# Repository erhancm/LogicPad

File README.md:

<h1 align="center">LogicPad</h1>

<p align="center">
  <strong>A programmable USB macro pad — and a desktop app that makes it yours.</strong><br>
  Assign macros, build lighting profiles, auto-switch layouts per app, back up your setups, and update firmware — all over USB.
</p>

<p align="center">

</p>

<p align="center">
  <a href="#-logicpad-configurator">Configurator</a> ·
  <a href="#-features">Features</a> ·
  <a href="#-hardware">Hardware</a> ·
  <a href="#-quick-start">Quick start</a> ·
  <a href="https://git.erhancm.com/erhan/LogicPad/releases">Download app</a>
</p>

---

## 💻 LogicPad configurator

LogicPad shows up as a standard USB keyboard when you plug it in, so it works without any software. The **Windows, macOS, and Linux** configurator app (built with Tauri 2) gives you a full-screen key editor, YAML profile packs, automatic profile switching based on which app you're using, and **firmware updates over USB**.

<table>
  <tr>
    <td colspan="2" align="center">
      
      <br><sub><b>Keys</b> — macros, chords, typed text, and drag-and-drop PC program launch</sub>
    </td>
  </tr>
  <tr>
    <td width="50%" align="center">
      
      <br><sub><b>Profiles</b> — wave, ripple, breathe &amp; rain lighting · per-key colours · OLED settings</sub>
    </td>
    <td width="50%" align="center">
      
      <br><sub><b>Auto-switch</b> — switch profiles when you focus or run specific apps</sub>
    </td>
  </tr>
</table>

### Try it without hardware

The app has a built-in simulated LogicPad so you can try everything without owning the physical board. Note that the software is still a work in progress — some features aren't implemented yet.

### Install the app

Download from **[Releases](https://git.erhancm.com/erhan/LogicPad/releases)**:

| Platform | Download | Install |
|----------|----------|---------|
| **Windows** | `LogicPad_*_x64-setup.exe` | Run the installer |
| **macOS** | `LogicPad_*_x64.dmg` | Open the DMG, drag LogicPad to Applications |
| **Linux** | `LogicPad_*_amd64.AppImage` | `chmod +x LogicPad_*.AppImage && ./LogicPad_*.AppImage` |
| **Linux** | `logicpad-app_*_amd64.deb` | `sudo apt install ./logicpad-app_*_amd64.deb` |
| **All** | `LogicPad-Productivity.yaml` | Import in the app (**Import…**) Example configuration |

**Linux note:** You'll need to install a [udev rule](04%20Software/logicpad-app/README.md#linux-udev) so the app has permission to communicate with the pad over USB. Without it, the app can't detect the device.

**Build from source:** `cd "04 Software/logicpad-app" && npm install && npm run build:app`

**Showcase demo:** [`04 Software/logicpad-app/showcase/`](04%20Software/logicpad-app/showcase/) comes with five pre-built profiles.

**Full app docs:** [`04 Software/logicpad-app/README.md`](04%20Software/logicpad-app/README.md)

---

## 🎯 Features

| | |
|---|---|
| **Keys** | A 3×3 grid of macro keys. Each key can trigger a keyboard shortcut, mouse click, media control or typed string (up to 240 bytes per key). You can also launch a PC program directly from a key. |
| **Profiles** | Create as many profiles as the internal flash allows. Each profile has its own lighting mode (wave, ripple, breathe, rain) or per-key RGB colours. |
| **Auto-switch** | A visual node graph lets you define rules like "when Spotify is focused, switch to the Media profile." Supports foreground-app and running-app checks, AND/OR logic gates.
| **YAML packs** | Export your entire setup — profiles, key mappings, and auto-switch rules — to a single YAML file. Import it later or share it with others. Use **Save as…** / **Import…** in the app. |
| **On-board bootloader** | Every board has a 4 KB USB HID bootloader. After the first flash, you can update firmware straight from the app — no ST-Link or disassembly needed. If something goes wrong, hold **SEL** while plugging in to enter recovery mode. |
| **On-device OLED editor** | Don't have the app? You can configure keys, profiles, and settings entirely from the pad's OLED screen using the selector and the nine keys as a d-pad. |
| **Plug-and-play HID** | LogicPad appears as a standard USB keyboard, mouse, and media device. No custom drivers needed on Windows, macOS, or Linux. |
| **Open hardware** | Full KiCad schematic and PCB layout. |

---

## 🔩 Hardware

<p align="center">
  <em>9 macro keys + selector · 0.96″ OLED · per-key RGB · STM32F103 · 3D-printable enclosure</em>
</p>

| Spec | Detail |
|------|--------|
| MCU | STM32F103C8 (ARM Cortex-M3) — 64 KB flash, 20 KB RAM |
| Keys | 9 macro keys + 1 selector button |
| Display | 0.96″ SSD1306 OLED, 128×64 pixels, connected over I²C |
| Lighting | Per-key RGB using 2020-size LEDs |
| USB | Composite HID device — keyboard + mouse + media controls + vendor-specific reports for app communication |
| Flash map | **4 KB** bootloader · **52 KB** application · **8 KB** persistent config store |

Current hardware revision: **V0.2** in [`02 Electronics/V0.2/`](02%20Electronics/V0.2/).

### Firmware updates

Every LogicPad board has a **4 KB USB HID bootloader** baked into flash. Once the board has been programmed for the first time, all future firmware updates happen over a regular USB cable — no ST-Link, no SWD debugger, and no need to open the enclosure.

**Updating firmware:**

1. Build the application firmware with the `Release` CMake preset in [`03 Firmware/Firmware/`](03%20Firmware/Firmware/).
2. Open the configurator app, click **Update firmware**, and select your `LogicPad.bin` file. The app communicates with the bootloader over USB HID and flashes the new image.

**Recovery:** If a firmware update fails or the app won't boot, hold the **SEL** button while plugging in the USB cable. This forces the board into bootloader mode so you can re-flash.

**First-time programming** still requires an ST-Link programmer (one-time only). The factory image `LogicPad_factory.hex` bundles both the bootloader and the application. See [`03 Firmware/bootloader/README.md`](03%20Firmware/bootloader/README.md) for details.

---

## 🚀 Quick start

### Daily use (no app needed)

1. **Plug in USB.** The host OS recognises LogicPad as a standard HID keyboard (plus mouse and media controls if you've configured them). No drivers, no pairing — it just works.

2. **Navigate the OLED menus.** A short press on the **selector** (SEL) button opens the on-device menu. Inside menus, the nine keys double as a d-pad for navigation:

   <table>
     <tr>
       <td width="55%">
         <table>
           <tr><th>Key</th><th>Action</th></tr>
           <tr><td>2</td><td>Up</td></tr>
           <tr><td>8</td><td>Down</td></tr>
           <tr><td>4</td><td>Left</td></tr>
           <tr><td>6</td><td>Right</td></tr>
           <tr><td>5</td><td>OK (select)</td></tr>
         </table>
         <p><strong>Short press SEL</strong> = go back one level. 
       </td>
       <td width="45%" align="center">
         
       </td>
     </tr>
   </table>

3. **Assign your macros.** Factory boards ship with empty key slots. You can assign macros either from the OLED menu (no PC required) or from the app. The app has more options.

### Build firmware from source

You'll need an ARM GCC toolchain and CMake. Both the bootloader and application firmware use CMake presets.

1. **Build the bootloader** — open [`03 Firmware/bootloader/`](03%20Firmware/bootloader/) and build with the `Release` CMake preset.
2. **Build the application** — open [`03 Firmware/Firmware/`](03%20Firmware/Firmware/) and build with the `Release` CMake preset.
3. **First-time flash** — combine bootloader + app into `LogicPad_factory.hex` and flash it via ST-Link (this is the only time you need ST-Link).
4. **All later updates** — just click **Update firmware** in the configurator app and point it at your new `LogicPad.bin`. The on-board bootloader handles the rest over USB.

---

## 📁 Repository layout

The repo is organised by discipline, numbered so it sorts in a logical order:

| Path | Contents |
|------|----------|
| [`01 Documentation/`](01%20Documentation/) | Hardware and protocol docs — MCU pinout, HID report format, OLED menu structure, and C4 architecture diagrams. |
| [`02 Electronics/V0.2/`](02%20Electronics/V0.2/) | KiCad schematic and PCB layout for the current board revision, plus BOM and Gerber files for manufacturing. |
| [`03 Firmware/Firmware/`](03%20Firmware/Firmware/) | Production firmware for the STM32F103. CMake-based build with ARM GCC. Handles USB HID, key scanning, OLED display, RGB lighting, and config storage. |
| [`03 Firmware/bootloader/`](03%20Firmware/bootloader/) | On-board USB HID bootloader. Occupies the first 4 KB of flash and allows firmware updates over USB without a debugger. |
| [`04 Software/logicpad-app/`](04%20Software/logicpad-app/) | Desktop configurator app — Tauri 2 (Rust + web frontend). Handles key editing, profile management, auto-switch rules, YAML import/export, and firmware updates. |
| [`05 Hardware/`](05%20Hardware/) | 3D-printable enclosure — STEP files for the case and button caps. |
| [`.github/assets/`](.github/assets/) | Images used in this README. |

---

## 📖 Documentation

- [Pinout](01%20Documentation/Pinout.md) — MCU pin assignments, key matrix wiring, OLED connections, and RGB data lines
- [HID protocol](01%20Documentation/HID_PROTOCOL.md) — USB HID report format and vendor-specific commands used by the configurator app
- [OLED UI](01%20Documentation/OLED_UI.md) — on-device menu structure and navigation flow
- [C4 architecture](01%20Documentation/C4_MODEL.md) — high-level system overview in C4 model notation

---

## 🤝 Contributing

Contributions are welcome — whether it's a bug report, a feature request, or a pull request. If you're planning a larger change, it's worth opening an issue first to discuss the approach. By contributing, you agree that your contributions will be licensed under [Apache 2.0](LICENSE).

---

## 🐛 Known issues

| Issue | Type | Status | Notes |
|-------|------|--------|-------|
| Sometimes you can't pan across the node editor when clicking on an empty area and dragging the mouse | Software | Open | Needs more investigation |
| OLED flicker or banding when taking pictures with camera| Software | Open | To do with refresh rate |
| Standby Clock setting is not persistant | Firmware | Open | When powering the unit off and on, the standby clock is reset to the default setting |
| Not all standby clock styles work | Software + Firmware | Open | Needs more investigation |
| LEDs can't reach full brightness in custom lighting modes | Hardware | Open | The LEDs are scanned one key at a time (1/9 duty cycle), so each LED is only actually on for a fraction of the time — the rest just looks lit because of persistence of vision. The STM32F103's GPIO pins can't source enough current to drive all 27 LEDs (9 keys × 3 colours) at once, so the per-LED brightness is capped by the scan rate. |

---

## 📝 To-do

| Feature | Type | Status | Notes |
|---------|------|--------|-------|
| Custom scripting assignable to each button | Software | Planned | Python/Lua scripts — TBD |
| Mouse and keyboard recording | Software | Planned | Record input sequences and replay them from a key |
| OCR-based automation | Software | Planned | Use image recognition to perform actions based on what's on screen |
| Long press functions | Software + Firmware | Planned | Different actions for short vs. long key presses |
| Profile hotkeys | Firmware | Planned | Assign a key to cycle through or jump to specific profiles instead of going through the on-board menu (temporarily override auto-switch condition) |

### Hardware V0.3

| Feature | Status | Notes |
|---------|--------|-------|
| Upgrade MCU to STM32F4 or RP2040 | Planned | More flash and RAM for larger configs, scripting support, and faster USB |
| USB-C connector | Planned | Replace the current Micro-USB with USB-C for better durability and reversibility |
| Hot-swap key sockets | Planned | Swap switches without soldering |
| Per-key addressable LEDs (WS2812B) | Planned | Remove the 1/9 scanning limitation and allow full brightness on all keys simultaneously |
| Larger OLED display | Planned | Upgrade from 0.96″ to 1.3″ for more readable menus and more info on screen |
| Rotary encoder | Planned | Add a clickable rotary encoder for volume control, scrolling, or menu navigation |
| Slider potentiometer | Planned | Linear slider for volume, brightness, or other continuous control |
| External flash storage | Planned | Dedicated flash chip or SD card slot — TBD. Would allow storing more profiles, macros, and recorded scripts on-device |
| Temperature and humidity sensor | Planned | Environmental sensor for ambient readings displayed on the OLED or used in automation rules. Including support for logging |

---

## 📄 License

This project is licensed under the [Apache License 2.0](LICENSE).

The third-party libraries bundled in `03 Firmware/Firmware/Drivers/` — namely the STM32 HAL, CMSIS, and ST's USB device library — are not covered by this license. They remain under their respective upstream licenses from STMicroelectronics and ARM.

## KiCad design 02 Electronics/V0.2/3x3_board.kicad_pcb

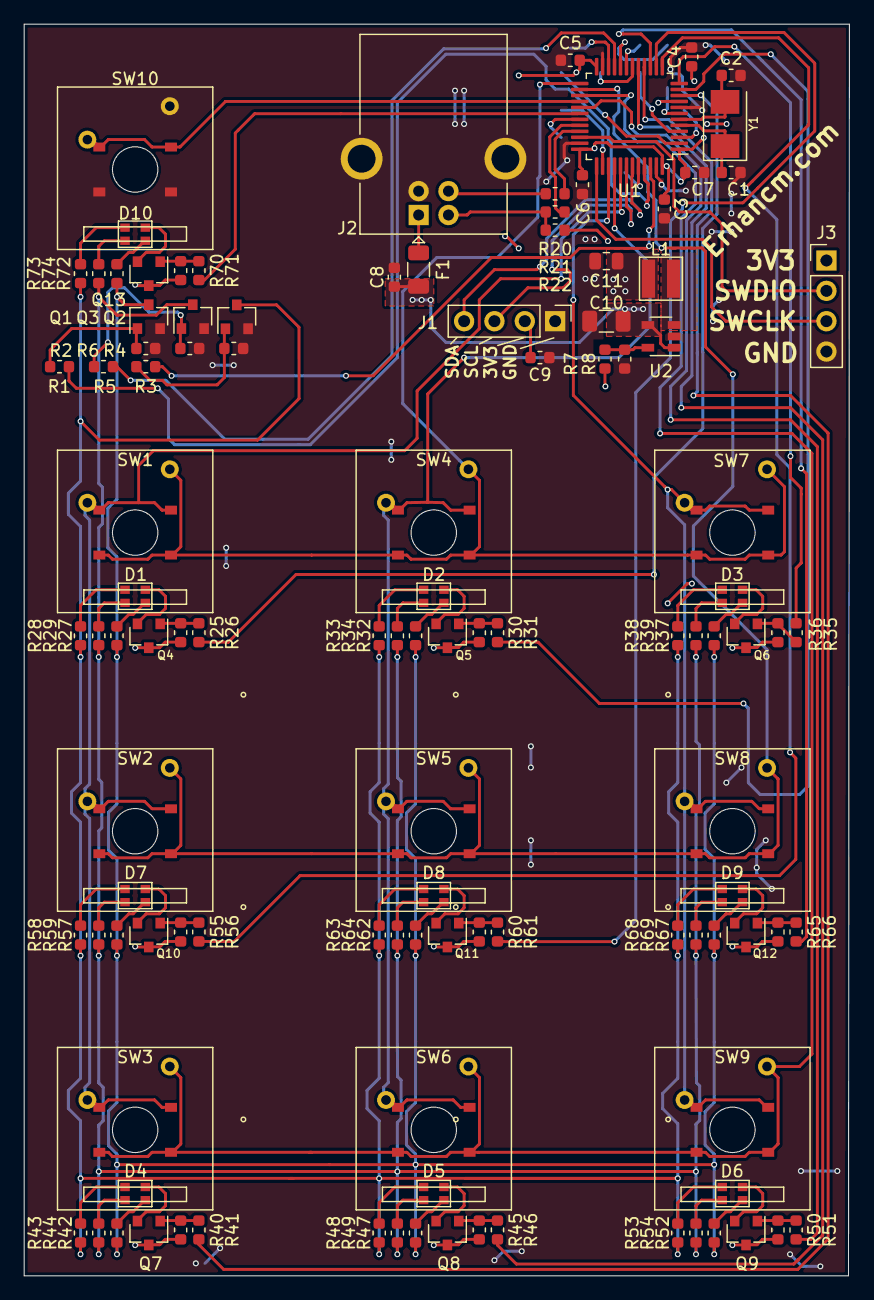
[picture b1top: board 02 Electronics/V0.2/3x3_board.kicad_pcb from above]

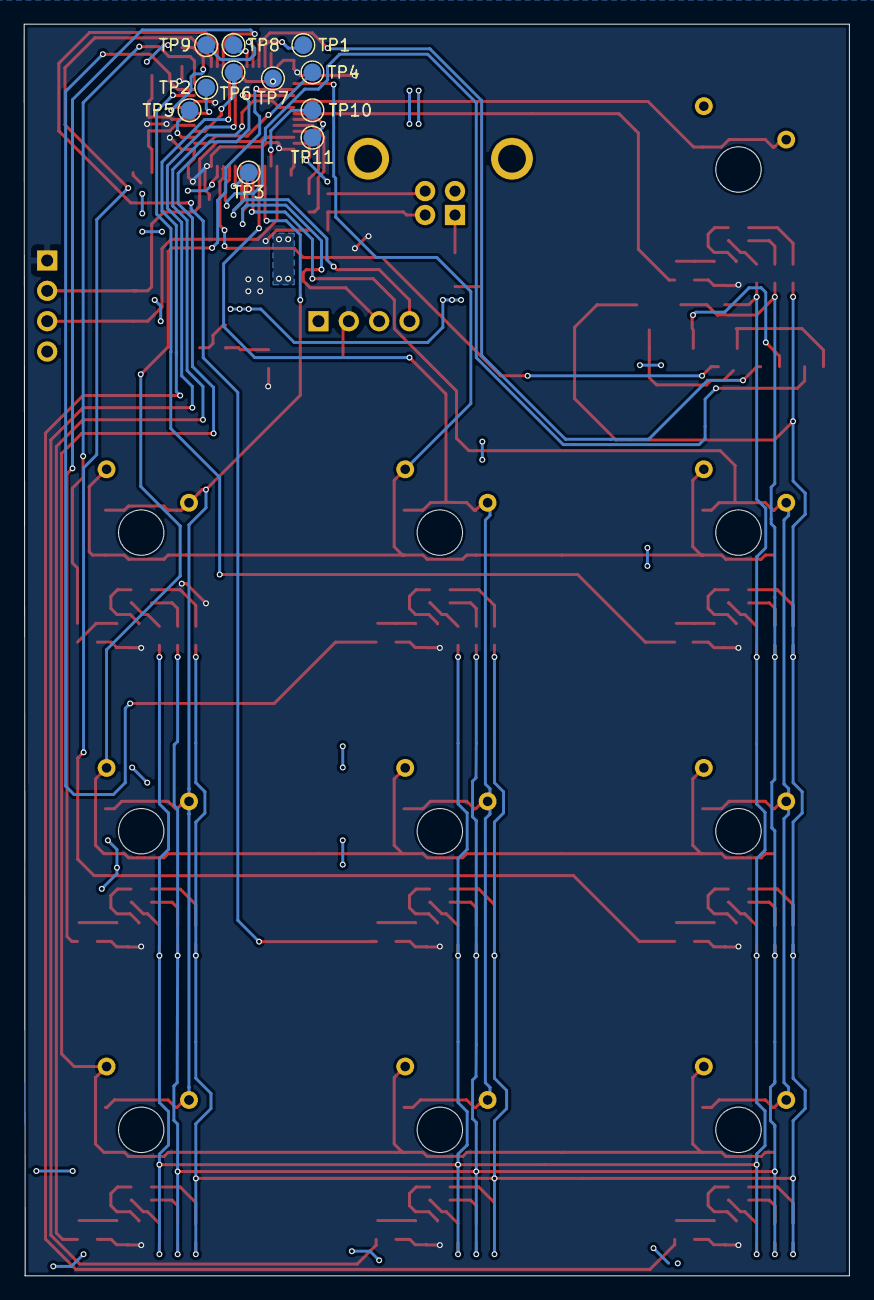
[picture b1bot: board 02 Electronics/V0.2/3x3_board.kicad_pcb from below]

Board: 2 copper layers, 69.1 x 104.8 mm, 124 parts (11 on the bottom side), 103 nets.

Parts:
C1, C2: 12pF; C_0603_1608Metric
C3, C4, C5, C6, C7, C8, C9: 100n; C_0603_1608Metric
C10: 4.7uF; C_1206_3216Metric
C11: 22uF; C_0805_2012Metric
D1, D2, D3, D4, D5, D6, D7, D8, D9, D10: RGB_LED; 2020_RGB
F1: Fuse; Fuse_1206_3216Metric
J1, J3: Conn_01x04; PinHeader_1x04_P2.54mm_Vertical
J2: USB_B; USB_B_OST_USB-B1HSxx_Horizontal
L1: 1uH; SRN3012TA-1R0Y
Q1, Q2, Q3: 2N7002; SOT-23
Q4, Q5, Q6, Q7, Q8, Q9, Q10, Q11, Q12, Q13: BSS84; SOT-23
R1, R3, R5, R26, R31, R36, R41, R46, R51, R56, R61, R66, R71: 100; R_0603_1608Metric
R2, R4, R6, R25, R30, R35, R40, R45, R50, R55, R60, R65, R70: 47k; R_0603_1608Metric
R7: 453K; R_0603_1608Metric
R8: 100K; R_0603_1608Metric
R20, R21: 22; R_0603_1608Metric
R22: 10K; R_0603_1608Metric
R27, R28, R29, R32, R33, R34, R37, R38, R39, R42, R43, R44, R47, R48, R49, R52, R53, R54, R57, R58, R59, R62, R63, R64, R67, R68, R69, R72, R73, R74: 165; R_0603_1608Metric
SW1, SW2, SW3, SW4, SW5, SW6, SW7, SW8, SW9, SW10: SW_Push; gateronSwitch
TP1, TP2, TP3, TP4, TP5, TP6, TP7, TP8, TP9, TP10, TP11: TestPoint_Probe; TestPoint_Pad_D1.5mm
U1: STM32F103C8Tx; LQFP-48_7x7mm_P0.5mm
U2: TLV62568DBV; SOT-23-5
Y1: 8Mhz; Crystal_SMD_5032-2Pin_5.0x3.2mm

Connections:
+3V3: C3.1, C4.1, C5.1, C6.1, C7.1, C9.2, C11.1, J1.2, J3.1, L1.2, Q4.3, Q5.3, Q6.3, Q7.3, Q8.3, Q9.3, Q10.3, Q11.3, Q12.3, Q13.3, R7.1, R22.1, R25.2, R30.2, R35.2, R40.2, R45.2, R50.2, R55.2, R60.2, R65.2, R70.2, U1.1, U1.9, U1.24, U1.36, U1.48
+5V: C8.1, C10.1, F1.1, U2.1, U2.4
/B_Ctrl: R5.1, U1.21
/BlueChannel: Q3.3, R29.2, R34.2, R39.2, R44.2, R49.2, R54.2, R59.2, R64.2, R69.2, R74.2
/C0R0: R26.1, U1.10
/C0R1: R31.1, U1.11
/C0R2: R36.1, U1.12
/C1R0: R56.1, U1.13
/C1R1: R61.1, U1.14
/C1R2: R66.1, U1.15
/C2R0: R41.1, U1.16
/C2R1: R46.1, U1.17
/C2R2: R51.1, U1.29
/Column_0: SW1.2, SW2.2, SW3.2, U1.41
/Column_1: SW4.2, SW5.2, SW6.2, U1.40
/Column_2: SW7.2, SW8.2, SW9.2, U1.39
/CtrlLed: R71.1, U1.30
/D+: R20.2, U1.33
/D-: R21.2, U1.32
/G_Ctrl: R3.1, U1.46
/GreenChannel: Q2.3, R28.2, R33.2, R38.2, R43.2, R48.2, R53.2, R58.2, R63.2, R68.2, R73.2
/I2C1_SCL: J1.3, U1.42
/I2C1_SDA: J1.4, U1.43
/R_Ctrl: R1.1, U1.45
/RedChannel: Q1.3, R27.2, R32.2, R37.2, R42.2, R47.2, R52.2, R57.2, R62.2, R67.2, R72.2
/Row_0: SW1.1, SW4.1, SW7.1, U1.25
/Row_1: SW2.1, SW5.1, SW8.1, U1.26
/Row_2: SW3.1, SW6.1, SW9.1, U1.27
/SWCLK: J3.3, U1.37
/SWDIO: J3.2, U1.34
/Selector: SW10.2, U1.28
/USB_D+: J2.3, R20.1
/USB_D-: J2.2, R21.1, R22.2
GND: C1.2, C2.2, C3.2, C4.2, C5.2, C6.2, C7.2, C8.2, C9.1, C10.2, C11.2, J1.1, J2.4, J2.5, J3.4, Q1.2, Q2.2, Q3.2, R2.2, R4.2, R6.2, R8.2, SW10.1, U1.8, U1.23, U1.35, U1.47, U2.2
unnamed: C1.1, U1.5, Y1.1
unnamed: C2.1, U1.6, Y1.2
unnamed: D1.1, R27.1
unnamed: D1.2, R29.1
unnamed: D1.3, Q4.2
unnamed: D1.4, R28.1
unnamed: D2.1, R32.1
unnamed: D2.2, R34.1
unnamed: D2.3, Q5.2
unnamed: D2.4, R33.1
unnamed: D3.1, R37.1
unnamed: D3.2, R39.1
unnamed: D3.3, Q6.2
unnamed: D3.4, R38.1
unnamed: D4.1, R42.1
unnamed: D4.2, R44.1
unnamed: D4.3, Q7.2
unnamed: D4.4, R43.1
unnamed: D5.1, R47.1
unnamed: D5.2, R49.1
unnamed: D5.3, Q8.2
unnamed: D5.4, R48.1
unnamed: D6.1, R52.1
unnamed: D6.2, R54.1
unnamed: D6.3, Q9.2
unnamed: D6.4, R53.1
unnamed: D7.1, R57.1
unnamed: D7.2, R59.1
unnamed: D7.3, Q10.2
unnamed: D7.4, R58.1
unnamed: D8.1, R62.1
unnamed: D8.2, R64.1
unnamed: D8.3, Q11.2
unnamed: D8.4, R63.1
unnamed: D9.1, R67.1
unnamed: D9.2, R69.1
unnamed: D9.3, Q12.2
unnamed: D9.4, R68.1
unnamed: D10.1, R72.1
unnamed: D10.2, R74.1
unnamed: D10.3, Q13.2
unnamed: D10.4, R73.1
unnamed: F1.2, J2.1
unnamed: L1.1, U2.3
unnamed: Q1.1, R1.2, R2.1
unnamed: Q2.1, R3.2, R4.1
unnamed: Q3.1, R5.2, R6.1
unnamed: Q4.1, R25.1, R26.2
unnamed: Q5.1, R30.1, R31.2
unnamed: Q6.1, R35.1, R36.2
unnamed: Q7.1, R40.1, R41.2
unnamed: Q8.1, R45.1, R46.2
unnamed: Q9.1, R50.1, R51.2
unnamed: Q10.1, R55.1, R56.2
unnamed: Q11.1, R60.1, R61.2
unnamed: Q12.1, R65.1, R66.2
unnamed: Q13.1, R70.1, R71.2
unnamed: R7.2, R8.1, U2.5
unnamed: TP1.1, U1.22
unnamed: TP2.1, U1.7
unnamed: TP3.1, U1.44
unnamed: TP4.1, U1.2
unnamed: TP5.1, U1.3
unnamed: TP6.1, U1.4
unnamed: TP7.1, U1.18
unnamed: TP8.1, U1.19
unnamed: TP9.1, U1.20
unnamed: TP10.1, U1.38
unnamed: TP11.1, U1.31

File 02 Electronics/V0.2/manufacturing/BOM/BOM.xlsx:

Comment | Designator | Footprint
SW_Push | SW1,SW7,SW8,SW10,SW9,SW6,SW5,SW4,SW3,SW2 | SMD
100K | R8 | R_0603_1608Metric
453K | R7 | R_0603_1608Metric
2N7002 | Q2,Q3,Q1 | SOT-23
100n | C9,C8,C7,C6,C5,C4,C3 | C_0603_1608Metric
TestPoint_Probe | TP11,TP10,TP9,TP8,TP7,TP6,TP5,TP4,TP3,TP2,TP1 | TestPoint_Pad_D1.5mm
8Mhz | Y1 | Crystal_SMD_5032-2Pin_5.0x3.2mm
165 | R74,R73,R72,R69,R68,R67,R64,R63,R62,R59,R58,R57,R54,R53,R52,R49,R48,R47,R44,R43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 | R_0603_1608Metric
100 | R71,R66,R61,R56,R51,R46,R41,R36,R31,R26,R5,R3,R1 | R_0603_1608Metric
47k | R70,R65,R60,R55,R50,R45,R40,R35,R30,R25,R6,R4,R2 | R_0603_1608Metric
BSS84 | Q13,Q12,Q11,Q10,Q9,Q8,Q7,Q6,Q5,Q4 | SOT-23
RGB_LED | D10,D9,D8,D7,D6,D5,D4,D3,D2,D1 | SMD
USB_B | J2 | USB_B_OST_USB-B1HSxx_Horizontal
TLV62568DBV | U2 | SOT-23-5
STM32F103C8Tx | U1 | LQFP-48_7x7mm_P0.5mm
10K | R22 | R_0603_1608Metric
22 | R21,R20 | R_0603_1608Metric
1uH | L1 | SRN3012TA-1R0Y
Conn_01x04 | J3,J1 | PinHeader_1x04_P2.54mm_Vertical
Fuse | F1 | Fuse_1206_3216Metric
22uF | C11 | C_0805_2012Metric
4.7uF | C10 | C_1206_3216Metric
12pF | C2,C1 | C_0603_1608Metric

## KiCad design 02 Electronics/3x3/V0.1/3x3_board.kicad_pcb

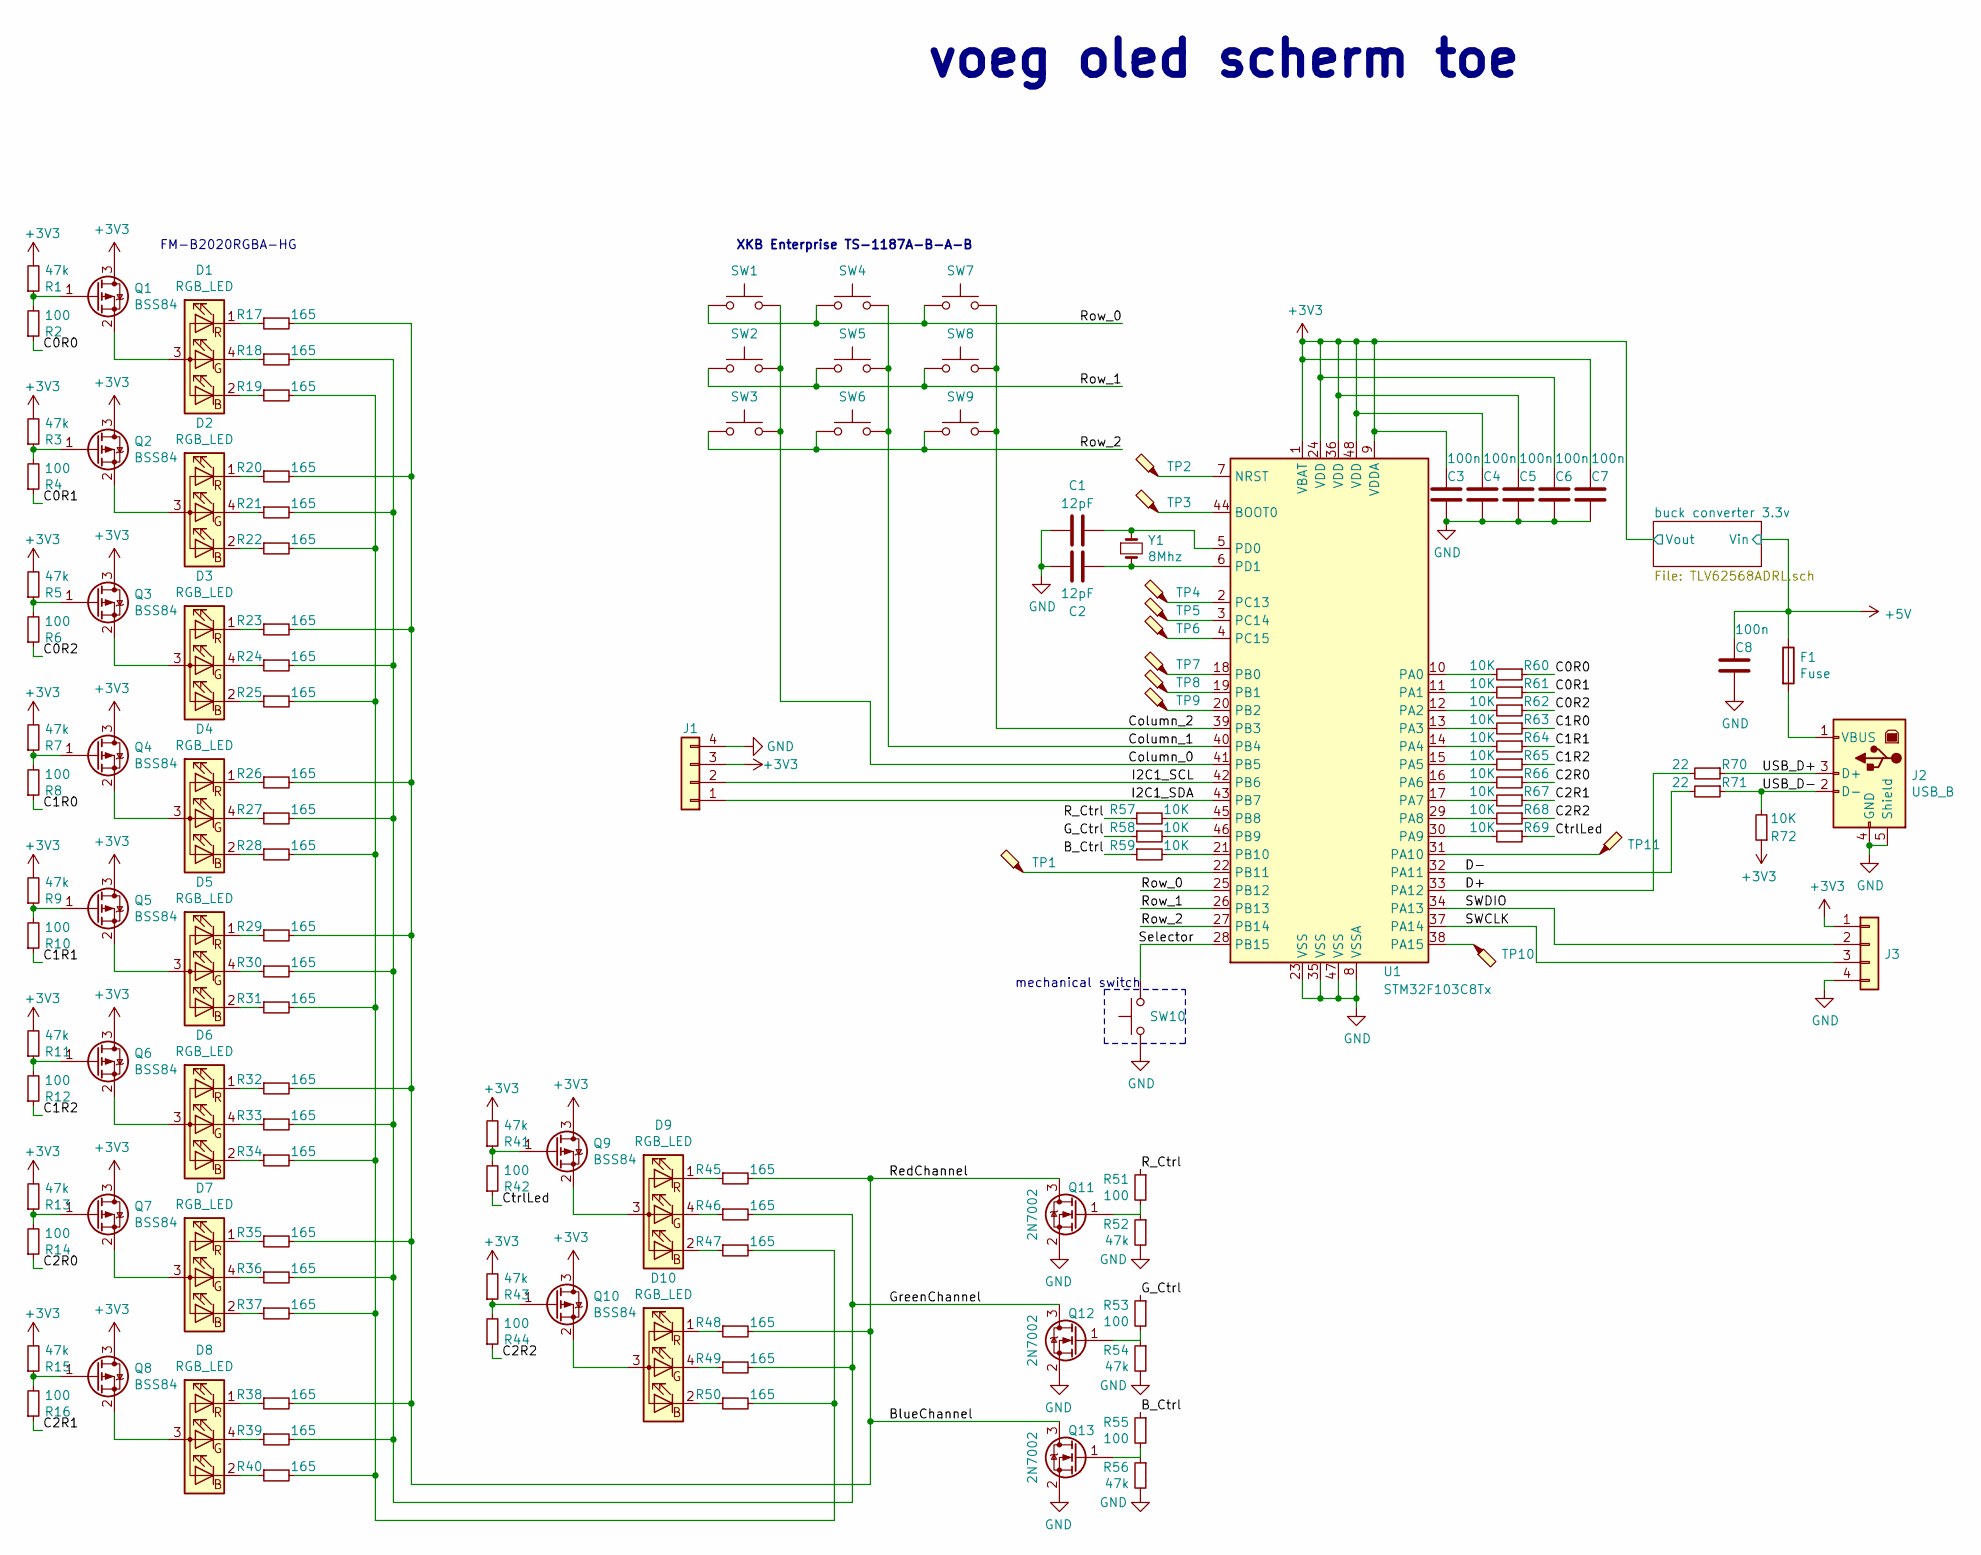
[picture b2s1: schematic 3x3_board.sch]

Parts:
C1, C2: 12pF; C_0603_1608Metric
C3, C4, C5, C6, C7, C8: 100n; C_0603_1608Metric
D1, D2, D3, D4, D5, D6, D7, D8, D9, D10: RGB_LED; 2020_RGB
F1: Fuse; Fuse_1206_3216Metric
J1, J3: Conn_01x04; PinHeader_1x04_P2.54mm_Vertical
J2: USB_B; USB_B_OST_USB-B1HSxx_Horizontal
Q1, Q2, Q3, Q4, Q5, Q6, Q7, Q8, Q9, Q10: BSS84; SOT-23
Q11, Q12, Q13: 2N7002; SOT-23
R1, R3, R5, R7, R9, R11, R13, R15, R41, R43, R52, R54, R56: 47k; R_0603_1608Metric
R2, R4, R6, R8, R10, R12, R14, R16, R42, R44, R51, R53, R55: 100; R_0603_1608Metric
R17, R18, R19, R20, R21, R22, R23, R24, R25, R26, R27, R28, R29, R30, R31, R32, R33, R34, R35, R36, R37, R38, R39, R40, R45, R46, R47, R48, R49, R50: 165; R_0603_1608Metric
R57, R58, R59, R60, R61, R62, R63, R64, R65, R66, R67, R68, R69, R72: 10K; R_0603_1608Metric
R70, R71: 22; R_0603_1608Metric
SW1, SW2, SW3, SW4, SW5, SW6, SW7, SW8, SW9, SW10: SW_Push; gateronSwitch
TP1, TP2, TP3, TP4, TP5, TP6, TP7, TP8, TP9, TP10, TP11: TestPoint_Probe; TestPoint_Loop_D1.80mm_Drill1.0mm_Beaded
U1: STM32F103C8Tx; LQFP-48_7x7mm_P0.5mm
Y1: 8Mhz; Crystal_SMD_5032-4Pin_5.0x3.2mm

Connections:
+3V3: C3.1, C4.1, C5.1, C6.1, C7.1, J1.3, J3.1, Q1.3 (D), Q2.3 (D), Q3.3 (D), Q4.3 (D), Q5.3 (D), Q6.3 (D), Q7.3 (D), Q8.3 (D), Q9.3 (D), Q10.3 (D), R1.2, R3.2, R5.2, R7.2, R9.2, R11.2, R13.2, R15.2, R41.2, R43.2, R72.1, U1.1 (VBAT), U1.9 (VDDA), U1.24 (VDD), U1.36 (VDD), U1.48 (VDD); also elsewhere on the board
+5V: C8.1, F1.1; also elsewhere on the board
/B_Ctrl: R55.1, R59.1
/BlueChannel: Q11.3 (D), Q13.3 (D), R17.2, R20.2, R23.2, R26.2, R29.2, R32.2, R35.2, R38.2, R45.2, R48.2
/C0R0: R2.1, R60.1
/C0R1: R4.1, R61.1
/C0R2: R6.1, R62.1
/C1R0: R8.1, R63.1
/C1R1: R10.1, R64.1
/C1R2: R12.1, R65.1
/C2R0: R14.1, R66.1
/C2R1: R16.1, R67.1
/C2R2: R44.1, R68.1
/Column_0: SW1.2, SW2.2, SW3.2, U1.41 (PB5)
/Column_1: SW4.2, SW5.2, SW6.2, U1.40 (PB4)
/Column_2: SW7.2, SW8.2, SW9.2, U1.39 (PB3)
/CtrlLed: R42.1, R69.1
/D+: R70.2, U1.33 (PA12)
/D-: R71.2, U1.32 (PA11)
/G_Ctrl: R53.1, R58.1
/GreenChannel: Q12.3 (D), R18.2, R21.2, R24.2, R27.2, R30.2, R33.2, R36.2, R39.2, R46.2, R49.2
/I2C1_SCL: J1.2, U1.42 (PB6)
/I2C1_SDA: J1.1, U1.43 (PB7)
/R_Ctrl: R51.1, R57.1
/Row_0: SW1.1, SW4.1, SW7.1, U1.25 (PB12)
/Row_1: SW2.1, SW5.1, SW8.1, U1.26 (PB13)
/Row_2: SW3.1, SW6.1, SW9.1, U1.27 (PB14)
/SWCLK: J3.3, U1.37 (PA14)
/SWDIO: J3.2, U1.34 (PA13)
/Selector: SW10.2, U1.28 (PB15)
/USB_D+: J2.3 (D+), R70.1
/USB_D-: J2.2 (D-), R71.1, R72.2
GND: C1.2, C2.2, C3.2, C4.2, C5.2, C6.2, C7.2, C8.2, J1.4, J2.4 (GND), J2.5 (Shield), J3.4, Q11.2 (S), Q12.2 (S), Q13.2 (S), R52.2, R54.2, R56.2, SW10.1, U1.8 (VSSA), U1.23 (VSS), U1.35 (VSS), U1.47 (VSS); also elsewhere on the board
unnamed: C1.1, U1.5 (PD0), Y1.1
unnamed: C2.1, U1.6 (PD1), Y1.2
unnamed: D1.1 (RK), R17.1
unnamed: D1.2 (BK), R19.1
unnamed: D1.3 (A), Q1.2 (S)
unnamed: D1.4 (GK), R18.1
unnamed: D2.1 (RK), R20.1
unnamed: D2.2 (BK), R22.1
unnamed: D2.3 (A), Q2.2 (S)
unnamed: D2.4 (GK), R21.1
unnamed: D3.1 (RK), R23.1
unnamed: D3.2 (BK), R25.1
unnamed: D3.3 (A), Q3.2 (S)
unnamed: D3.4 (GK), R24.1
unnamed: D4.1 (RK), R26.1
unnamed: D4.2 (BK), R28.1
unnamed: D4.3 (A), Q4.2 (S)
unnamed: D4.4 (GK), R27.1
unnamed: D5.1 (RK), R29.1
unnamed: D5.2 (BK), R31.1
unnamed: D5.3 (A), Q5.2 (S)
unnamed: D5.4 (GK), R30.1
unnamed: D6.1 (RK), R32.1
unnamed: D6.2 (BK), R34.1
unnamed: D6.3 (A), Q6.2 (S)
unnamed: D6.4 (GK), R33.1
unnamed: D7.1 (RK), R35.1
unnamed: D7.2 (BK), R37.1
unnamed: D7.3 (A), Q7.2 (S)
unnamed: D7.4 (GK), R36.1
unnamed: D8.1 (RK), R38.1
unnamed: D8.2 (BK), R40.1
unnamed: D8.3 (A), Q8.2 (S)
unnamed: D8.4 (GK), R39.1
unnamed: D9.1 (RK), R45.1
unnamed: D9.2 (BK), R47.1
unnamed: D9.3 (A), Q9.2 (S)
unnamed: D9.4 (GK), R46.1
unnamed: D10.1 (RK), R48.1
unnamed: D10.2 (BK), R50.1
unnamed: D10.3 (A), Q10.2 (S)
unnamed: D10.4 (GK), R49.1
unnamed: F1.2, J2.1 (VBUS)
unnamed: Q1.1 (G), R1.1, R2.2
unnamed: Q2.1 (G), R3.1, R4.2
unnamed: Q3.1 (G), R5.1, R6.2
unnamed: Q4.1 (G), R7.1, R8.2
unnamed: Q5.1 (G), R9.1, R10.2
unnamed: Q6.1 (G), R11.1, R12.2
unnamed: Q7.1 (G), R13.1, R14.2
unnamed: Q8.1 (G), R15.1, R16.2
unnamed: Q9.1 (G), R41.1, R42.2
unnamed: Q10.1 (G), R43.1, R44.2
unnamed: Q11.1 (G), R51.2, R52.1
unnamed: Q12.1 (G), R53.2, R54.1
unnamed: Q13.1 (G), R55.2, R56.1
unnamed: R19.2, R22.2, R25.2, R28.2, R31.2, R34.2, R37.2, R40.2, R47.2, R50.2
unnamed: R57.2, U1.45 (PB8)
unnamed: R58.2, U1.46 (PB9)
unnamed: R59.2, U1.21 (PB10)
unnamed: R60.2, U1.10 (PA0)
unnamed: R61.2, U1.11 (PA1)
unnamed: R62.2, U1.12 (PA2)
unnamed: R63.2, U1.13 (PA3)
unnamed: R64.2, U1.14 (PA4)
unnamed: R65.2, U1.15 (PA5)
unnamed: R66.2, U1.16 (PA6)
unnamed: R67.2, U1.17 (PA7)
unnamed: R68.2, U1.29 (PA8)
unnamed: R69.2, U1.30 (PA9)
unnamed: TP1.1, U1.22 (PB11)
unnamed: TP2.1, U1.7 (NRST)
unnamed: TP3.1, U1.44 (BOOT0)
unnamed: TP4.1, U1.2 (PC13)
unnamed: TP5.1, U1.3 (PC14)
unnamed: TP6.1, U1.4 (PC15)
unnamed: TP7.1, U1.18 (PB0)
unnamed: TP8.1, U1.19 (PB1)
unnamed: TP9.1, U1.20 (PB2)
unnamed: TP10.1, U1.38 (PA15)
unnamed: TP11.1, U1.31 (PA10)

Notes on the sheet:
FM-B2020RGBA-HG
mechanical switch
voeg oled scherm toe
XKB Enterprise TS-1187A-B-A-B

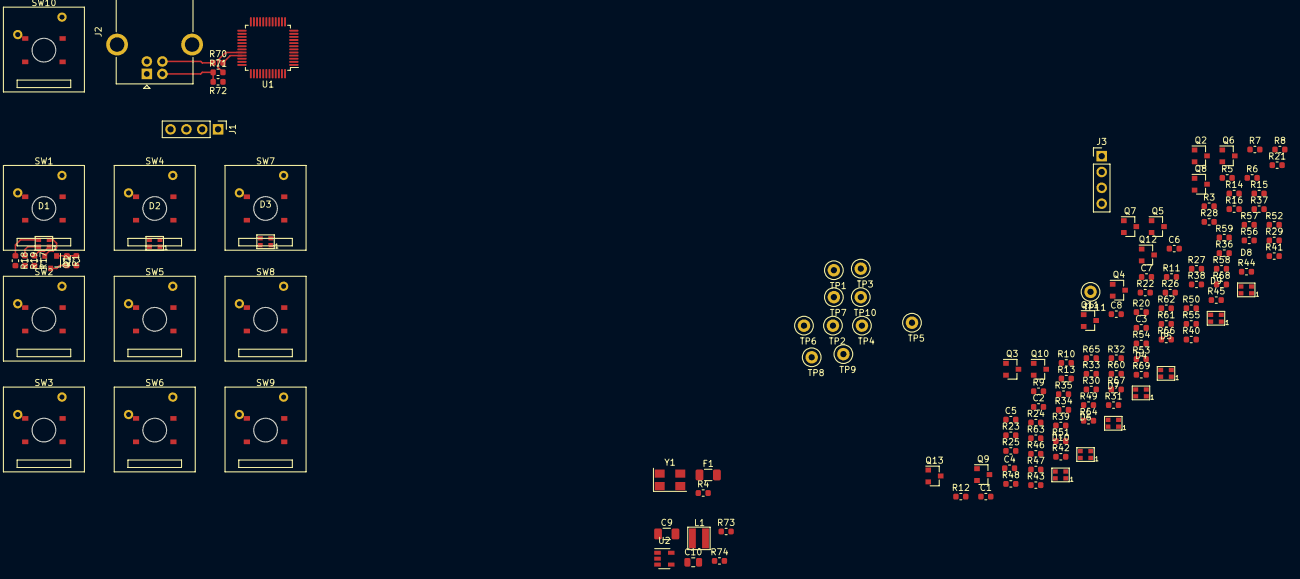
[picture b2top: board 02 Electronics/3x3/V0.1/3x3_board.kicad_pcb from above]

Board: 2 copper layers, 136 parts (0 on the bottom side), 116 nets.

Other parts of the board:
C9: 4.7uF; C_1206_3216Metric
C10: 22uF; C_0805_2012Metric
L1: 1uH; SRN3012TA-1R0Y
R73: 453K; R_0603_1608Metric
R74: 100K; R_0603_1608Metric
U2: TLV62568DBV; SOT-23-5

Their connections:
+3V3: C10.1, L1.2, R73.1; also elsewhere on the board
+5V: C9.1, U2.1, U2.4; also elsewhere on the board
GND: C9.2, C10.2, R74.2, U2.2; also elsewhere on the board
unnamed: L1.1, U2.3
unnamed: R73.2, R74.1, U2.5

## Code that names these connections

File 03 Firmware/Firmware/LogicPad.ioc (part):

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Mcu.Name=STM32F103C(8-B)Tx
Mcu.Package=LQFP48
Mcu.UserName=STM32F103C8Tx
PA0-WKUP.GPIOParameters=GPIO_PuPd,GPIO_Label
PA0-WKUP.GPIO_Label=C0R0
PA0-WKUP.GPIO_PuPd=GPIO_PULLUP
PA0-WKUP.Signal=GPIO_Output
PA1.GPIOParameters=GPIO_PuPd,GPIO_Label
PA1.GPIO_Label=C0R1
PA1.GPIO_PuPd=GPIO_PULLUP
PA1.Signal=GPIO_Output
PA11.Mode=Device
PA11.Signal=USB_DM
PA12.Mode=Device
PA12.Signal=USB_DP
PA13.Mode=Serial_Wire
PA13.Signal=SYS_JTMS-SWDIO
PA14.Mode=Serial_Wire
PA14.Signal=SYS_JTCK-SWCLK
PA2.GPIOParameters=GPIO_PuPd,GPIO_Label
PA2.GPIO_Label=C0R2
PA2.GPIO_PuPd=GPIO_PULLUP
PA2.Signal=GPIO_Output
PA3.GPIOParameters=GPIO_PuPd,GPIO_Label
PA3.GPIO_Label=C1R0
PA3.GPIO_PuPd=GPIO_PULLUP
PA3.Signal=GPIO_Output
PA4.GPIOParameters=GPIO_PuPd,GPIO_Label
PA4.GPIO_Label=C1R1
PA4.GPIO_PuPd=GPIO_PULLUP
PA4.Signal=GPIO_Output
PA5.GPIOParameters=GPIO_PuPd,GPIO_Label
PA5.GPIO_Label=C1R2
PA5.GPIO_PuPd=GPIO_PULLUP
PA5.Signal=GPIO_Output
PA6.GPIOParameters=GPIO_PuPd,GPIO_Label
PA6.GPIO_Label=C2R0
PA6.GPIO_PuPd=GPIO_PULLUP
PA6.Signal=GPIO_Output
PA7.GPIOParameters=PinState,GPIO_PuPd,GPIO_Label
PA7.GPIO_Label=C2R1
PA7.GPIO_PuPd=GPIO_PULLUP
PA7.PinState=GPIO_PIN_RESET
PA7.Signal=GPIO_Output
PA8.GPIOParameters=GPIO_PuPd,GPIO_Label
PA8.GPIO_Label=C2R2
PA8.GPIO_PuPd=GPIO_PULLUP
PA8.Signal=GPIO_Output
PA9.GPIOParameters=GPIO_PuPd,GPIO_Label
PA9.GPIO_Label=CtrlLed
PA9.GPIO_PuPd=GPIO_PULLDOWN
PA9.Signal=GPIO_Output
PB10.GPIOParameters=GPIO_PuPd,GPIO_Label
PB10.GPIO_Label=B_Ctrl
PB10.GPIO_PuPd=GPIO_PULLDOWN
PB10.Signal=GPIO_Output
PB12.GPIOParameters=GPIO_PuPd,GPIO_Label
PB12.GPIO_Label=Row_0
PB12.GPIO_PuPd=GPIO_PULLUP
PB12.Signal=GPIO_Input
PB13.GPIOParameters=GPIO_PuPd,GPIO_Label
PB13.GPIO_Label=Row_1
PB13.GPIO_PuPd=GPIO_PULLUP
PB13.Signal=GPIO_Input
PB14.GPIOParameters=GPIO_PuPd,GPIO_Label
PB14.GPIO_Label=Row_2
PB14.GPIO_PuPd=GPIO_PULLUP
PB14.Signal=GPIO_Input
PB15.GPIOParameters=GPIO_PuPd,GPIO_Label
PB15.GPIO_Label=Selector
PB15.GPIO_PuPd=GPIO_PULLUP
PB15.Signal=GPIO_Input
PB3.GPIOParameters=GPIO_PuPd,GPIO_Label
PB3.GPIO_Label=Column_2
PB3.GPIO_PuPd=GPIO_NOPULL
PB3.Signal=GPIO_Output
PB4.GPIOParameters=GPIO_PuPd,GPIO_Label
PB4.GPIO_Label=Column_1
PB4.GPIO_PuPd=GPIO_NOPULL
PB4.Signal=GPIO_Output
PB5.GPIOParameters=GPIO_PuPd,GPIO_Label
PB5.GPIO_Label=Column_0
PB5.GPIO_PuPd=GPIO_NOPULL
PB5.Signal=GPIO_Output
PB6.Mode=I2C
PB6.Signal=I2C1_SCL
PB7.Mode=I2C
PB7.Signal=I2C1_SDA
PB8.GPIOParameters=PinState,GPIO_PuPd,GPIO_Label
PB8.GPIO_Label=R_Ctrl
PB8.GPIO_PuPd=GPIO_PULLDOWN
PB8.PinState=GPIO_PIN_RESET
PB8.Signal=GPIO_Output
PB9.GPIOParameters=GPIO_PuPd,GPIO_Label
PB9.GPIO_Label=G_Ctrl
PB9.GPIO_PuPd=GPIO_PULLDOWN
PB9.Signal=GPIO_Output
PD0-OSC_IN.Mode=HSE-External-Oscillator
PD0-OSC_IN.Signal=RCC_OSC_IN
PD1-OSC_OUT.Mode=HSE-External-Oscillator
PD1-OSC_OUT.Signal=RCC_OSC_OUT
RCC.SYSCLKFreq_VALUE=72000000
RCC.SYSCLKSource=RCC_SYSCLKSOURCE_PLLCLK
board=custom

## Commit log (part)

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2025-10-02 add testfile
    just a test of gitea
2025-10-05 Sync with old project
2025-10-05 Complete Sync
2025-10-06 Fix schematic
2025-10-06 add files to the gitignore
2025-10-06 Removed V0.3 prototype we don't need anymore.
2025-10-06 - Segregated old firmware - Removed un needed files
2025-10-06 Removed nested folder structure
2025-10-06 more folder organisation activity in the FW section
2025-10-07 Initial firmware. Not configured correctly yet
2025-10-07 Pins defined
2025-10-07 I2C Setup.
2025-10-07 Add PIN_CONFIGURATION detailing the purposes of the pins
2025-10-07 Create LED Test Routine
2025-10-08 fix led test all test routine
2025-10-08 PIN pull up and pull down defined
2025-10-08 pull ups for button inputs defined
2025-10-08 Add turn OFF time during LED_Test_All
2025-10-08 fix missing include
2025-10-09 add ctrlled to test all led routine + change some pins to pull up type
2025-10-10 Rename LED Test files to LED Control
2025-10-12 Removed led_test_individual functions
2025-10-12 added USB custom HID (not implemented)
2025-10-12 project tracker created

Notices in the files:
README.md:
License: Apache 2.0
